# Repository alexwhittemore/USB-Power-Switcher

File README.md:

USB-Power-Switcher
==================

Simple relay-driven design to interrupt power to a USB device/tree.

This board allows an arbitrary single-ended signal (voltage dependant on how you populate the base resistor) to control power to a USB device at an A connection, both normally open and normally closed operation supported.

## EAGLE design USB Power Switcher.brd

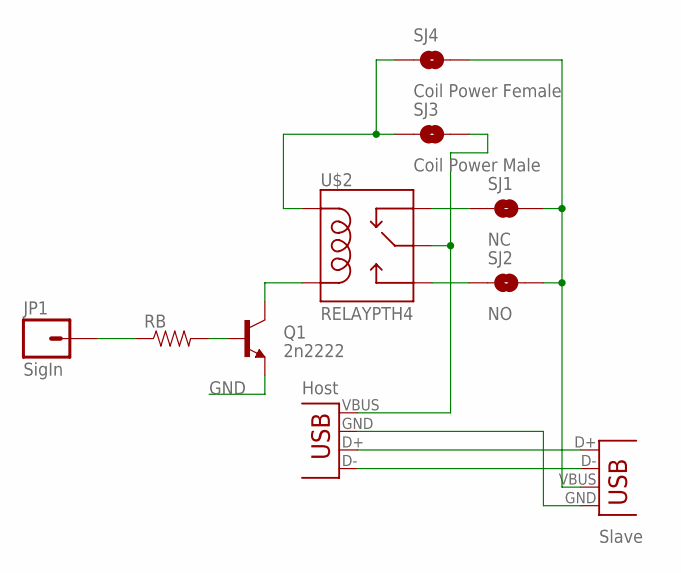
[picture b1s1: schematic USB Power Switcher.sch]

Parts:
JP1: SigIn; 1X01
Q1: 2n2222; TO-92-AMMO
RB: RESISTORAXIAL-0.3; AXIAL-0.3
SJ1: NC; SJ_2S_BIG
SJ2: NO; SJ_2S_BIG
SJ3: Coil Power Male; SJ_2S-NO
SJ4: Coil Power Female; SJ_2S-NO
U$2: RELAYPTH4; RELAY-JZC
X1: USB-A-SMD; USB-A-S-NOSILK-FEMALE
X2: USB-A-H

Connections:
DM: X1.D-, X2.D- (D+)
DP: X1.D+, X2.D+ (D-)
GND: Q1.1 (E), X1.GND, X2.GND (VBUS)
unnamed: SJ3.1, SJ4.1, U$2.5 (COIL1)
unnamed: Q1.3 (C), U$2.1 (COIL2)
unnamed: Q1.2 (B), RB.P$2 (2)
unnamed: JP1.1, RB.P$1 (1)
unnamed: SJ2.1, U$2.3 (NO)
unnamed: SJ1.1, U$2.2 (NC)
VBHOST: SJ3.2, U$2.4 (MAIN), X2.VBUS (GND)
VBSLAVE: SJ1.2, SJ2.2, SJ4.2, X1.VBUS

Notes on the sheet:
Host
Slave

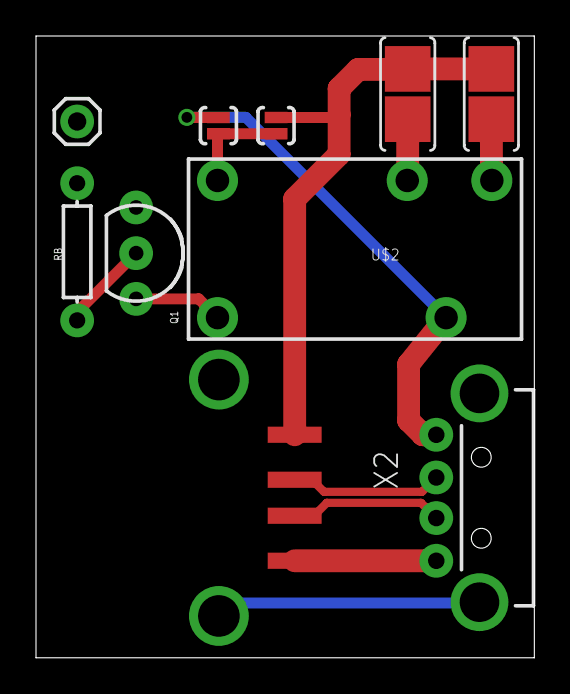
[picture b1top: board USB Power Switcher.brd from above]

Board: 2 copper layers, 27.7 x 34.5 mm, 10 parts (0 on the bottom side), 11 nets.

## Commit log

2013-06-22 Initial revision of USB Power Switcher

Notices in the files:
USB Power Switcher.brd:
CC-BY-SA 3.0
parts and their libraries:
SparkFun-Connectors: Licensing: CC v3.0 Share-Alike You are welcome to use this library for commercial purposes.
AlexW-Eagle-Libraries: Released under the Creative Commons
AlexW-Eagle-Libraries: http://creativecommons.org/licenses/by-sa/3.0
